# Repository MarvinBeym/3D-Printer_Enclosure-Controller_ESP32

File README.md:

# 3D Printer Enclosure Controller ESP32

***
This is an enclosure controller for 3d printers that runs on the dual core ESP32.

- It uses a Nextion NX4832T035 3.5inch 480px320p color touch TFT display.
- It also includes a simple Webinterface made with ESPUI for quick access without having to go to the display.

- ***For detailed information and images please see the [Wiki](https://github.com/MarvinBeym/3D-Printer_Enclosure-Controller_ESP32/wiki "Wiki").***
- ***STL files for 3D-Printing can be found on [Thingiverse](https://www.thingiverse.com/thing:4582196 "Thingiverse")***
***
You can currently choose between 2 versions.
1. The older cnc version
This is a bit older (the first one I made). Features haven't changed yet.
This is the version you want If you want to mill the pcb with a cnc mill because it is single side and has wider traces to make it easier for your mill.
2. The newest, pretiest pcb version
This is supposed to be made by a pcb factory like jlcpcb
It has text on it for all the components.
It also looks way better (I recommend ordering in black :D)

If you choose 2. -> I ordered mine from JLCPCB. The Gerber files are inside the Eagle folder (Gerber(vx.x.x).7z)
These were exported with the premade jlcpcb double sided cam processor. So you can just upload them to jlcpcb and order them.

***This project consists of 4 parts.***
1. The ESP32 software.
2. The Nextion display software (text, icons, images, ...).
3. The PCB.
4. The 3D Printed case to house everything.

***Features of this controller are:***
- 2x temperature and humidity sensors (DHT22).
- 2x 4-pin pwm fans.
- 1x Buzzer for alarms, warnings and such (currently not implemented as of v1.3.1).
- 1x 12v led strip connection controlled by a relay. This is usefull if you want to have a single color (like white).
- 1x 5V WS2812B single addressable led strip

***Software features:***
- ESPUI webinterface
- WifiManager creates a hotspot you can connect to that will make it possible to set the wifi network to connect to on boot.
- All values that can be changed can also be stored to flash. These values will be retrieved at boot and only saved using button pressed to prevent flash wear.
- Displaying of fan speed and percent.
- The possibility to change the speed of fans from 0% - 100%
- Displaying of sensor humidity and temperature
- Switching of 12v led strip.
- Graph for temperatures (only nextion display currently)
- Multiple modes choosable for WS2812B
  - (rainbow, fate, pulse, temperature (led strip is split in half showing temperature in color), running)
- Multiple colors choosable for WS2812B
- LCD Brighness
- LCD Sleep
- Temperature Warning and Danger 
  - (Currently do the same)
  - At some point Danger warning is supposed to do everything to make your notice something going wrong.
  - Like buzzer alarm, led blinking, display blinking and such. This is supposed to be used when something is seriously wrong > xyzTemperature.

***Notices:***
- The board uses a XL4015 buck converter which is rated for ~5A of power. 
- Make sure to choose an led strip that won't overload the converter. As this could lead to overheating.
- Also make sure to leave a bit of room for all other components like fans, 12v led strip, sensors and display.

- It is expecially important to make sure the Nextion display gets enough power.
- If your display starts showing weird graphics. DISCONNECT power immediately.
- Don't run the pcb from 5V pc usb port.
- Low current can destroy the display (although it never happened to me).

- Fan rpm could be off a bit as tacho reading is influenced by noise.
- The tacho ports both have an rc filter and most fans will work without a problem and will display the correct value.
- I have one fan (NF-F12 industrialPPC-3000) that will always display > 4500rpm. 
  - (should only have 3000rpm). 
  - I'm not sure if that is something caused by the fan itself.

***Credits:***
- Icons shown on the Nextion display are from https://icons8.com/

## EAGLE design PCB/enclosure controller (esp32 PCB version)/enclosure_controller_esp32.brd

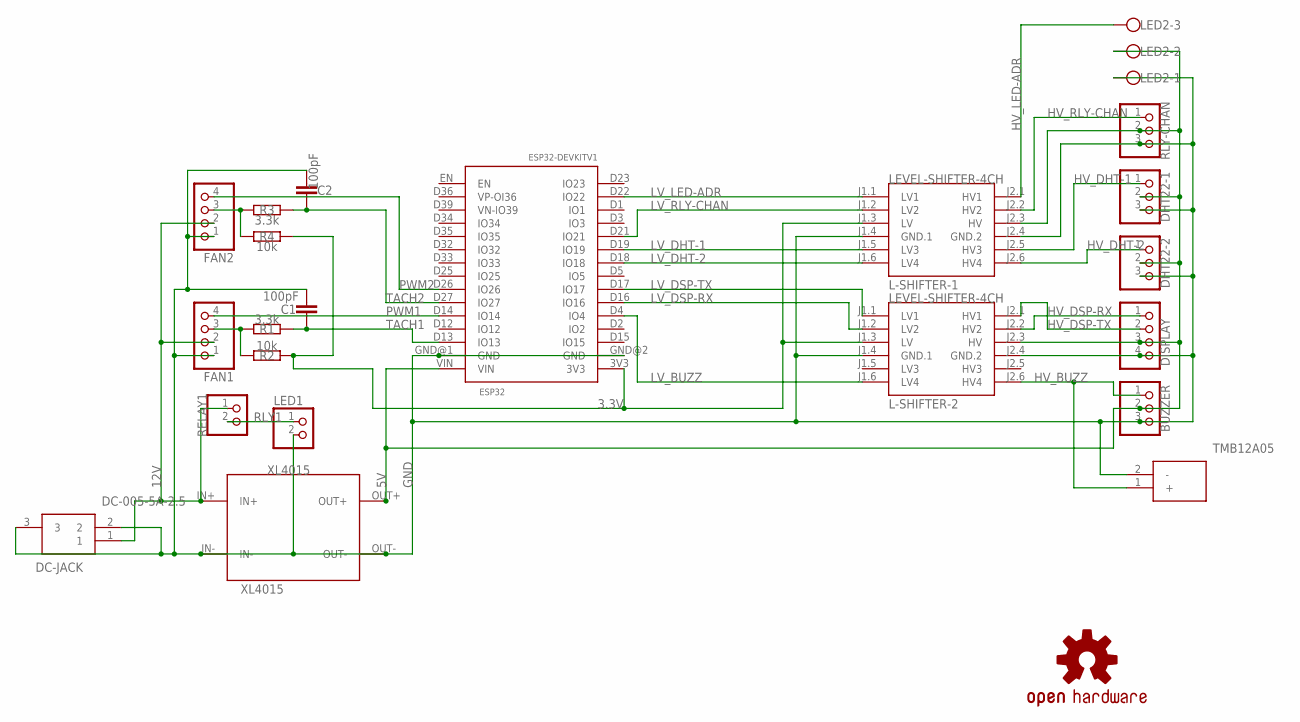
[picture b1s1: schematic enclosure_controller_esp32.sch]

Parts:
BUZZER: PINHD-1X3/OCT; 1X03/OCT
C1, C2: 100pF; C050-025X075
DC-JACK: DC-005-5A-2.5; DC0055A25
DHT22-1, DHT22-2: PINHD-1X3/OCT; 1X03/OCT
DISPLAY: PINHD-1X4/OCT; 1X04/OCT
ESP32: ESP32DEVKITV1; ESP32-DEVKITV1
FAN1, FAN2: PINHD-1X4/OCT; 1X04/OCT
L-SHIFTER-1, L-SHIFTER-2: LEVEL-SHIFTER-4CH
LED1: PINHD-1X2/OCT; 1X02/OCT
LED2: LED2-ADR; W237-103
LOGO1: OSHW-LOGOM; OSHW-LOGO-M
LS1: TMB12A05
R1, R3: 3.3k; 0207/10
R2, R4: 10k; 0207/10
RELAY1: PINHD-1X2/OCT; 1X02/OCT
RLY-CHAN: PINHD-1X3/OCT; 1X03/OCT
XL4015: XL4015

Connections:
3.3V: ESP32.3V3, L-SHIFTER-1.J1.3 (LV), L-SHIFTER-2.J1.3 (LV), R2.1, R4.1
5V: BUZZER.2, DHT22-1.2, DHT22-2.2, DISPLAY.3, ESP32.VIN, L-SHIFTER-1.J2.3 (HV), L-SHIFTER-2.J2.3 (HV), LED2.2, RLY-CHAN.2, XL4015.OUT+
12V: DC-JACK.1, FAN1.2, FAN2.2, RELAY1.1, XL4015.IN+
GND: BUZZER.3, C1.2, C2.1, DC-JACK.2, DC-JACK.3, DHT22-1.3, DHT22-2.3, DISPLAY.4, ESP32.GND@1 (GND), ESP32.GND@2 (GND), FAN1.1, FAN2.1, L-SHIFTER-1.J1.4 (GND.1), L-SHIFTER-1.J2.4 (GND.2), L-SHIFTER-2.J1.4 (GND.1), L-SHIFTER-2.J2.4 (GND.2), LED1.2, LED2.1, LS1.2 (-), RLY-CHAN.3, XL4015.IN-, XL4015.OUT-
HV_BUZZ: BUZZER.1, L-SHIFTER-2.J2.6 (HV4), LS1.1 (+)
HV_DHT-1: DHT22-1.1, L-SHIFTER-1.J2.5 (HV3)
HV_DHT-2: DHT22-2.1, L-SHIFTER-1.J2.6 (HV4)
HV_DSP-RX: DISPLAY.1, L-SHIFTER-2.J2.2 (HV2)
HV_DSP-TX: DISPLAY.2, L-SHIFTER-2.J2.1 (HV1)
HV_LED-ADR: L-SHIFTER-1.J2.1 (HV1), LED2.3
HV_RLY-CHAN: L-SHIFTER-1.J2.2 (HV2), RLY-CHAN.1
LV_BUZZ: ESP32.D4 (IO4), L-SHIFTER-2.J1.6 (LV4)
LV_DHT-1: ESP32.D19 (IO19), L-SHIFTER-1.J1.5 (LV3)
LV_DHT-2: ESP32.D18 (IO18), L-SHIFTER-1.J1.6 (LV4)
LV_DSP-RX: ESP32.D16 (IO16), L-SHIFTER-2.J1.2 (LV2)
LV_DSP-TX: ESP32.D17 (IO17), L-SHIFTER-2.J1.1 (LV1)
LV_LED-ADR: ESP32.D22 (IO22), L-SHIFTER-1.J1.1 (LV1)
LV_RLY-CHAN: ESP32.D21 (IO21), L-SHIFTER-1.J1.2 (LV2)
PWM1: ESP32.D14 (IO14), FAN1.4
PWM2: ESP32.D26 (IO26), FAN2.4
RLY1: LED1.1, RELAY1.2
TACH1: C1.1, ESP32.D13 (IO13), FAN1.3, R1.1, R1.2, R2.2
TACH2: C2.2, ESP32.D27 (IO27), FAN2.3, R3.1, R3.2, R4.2

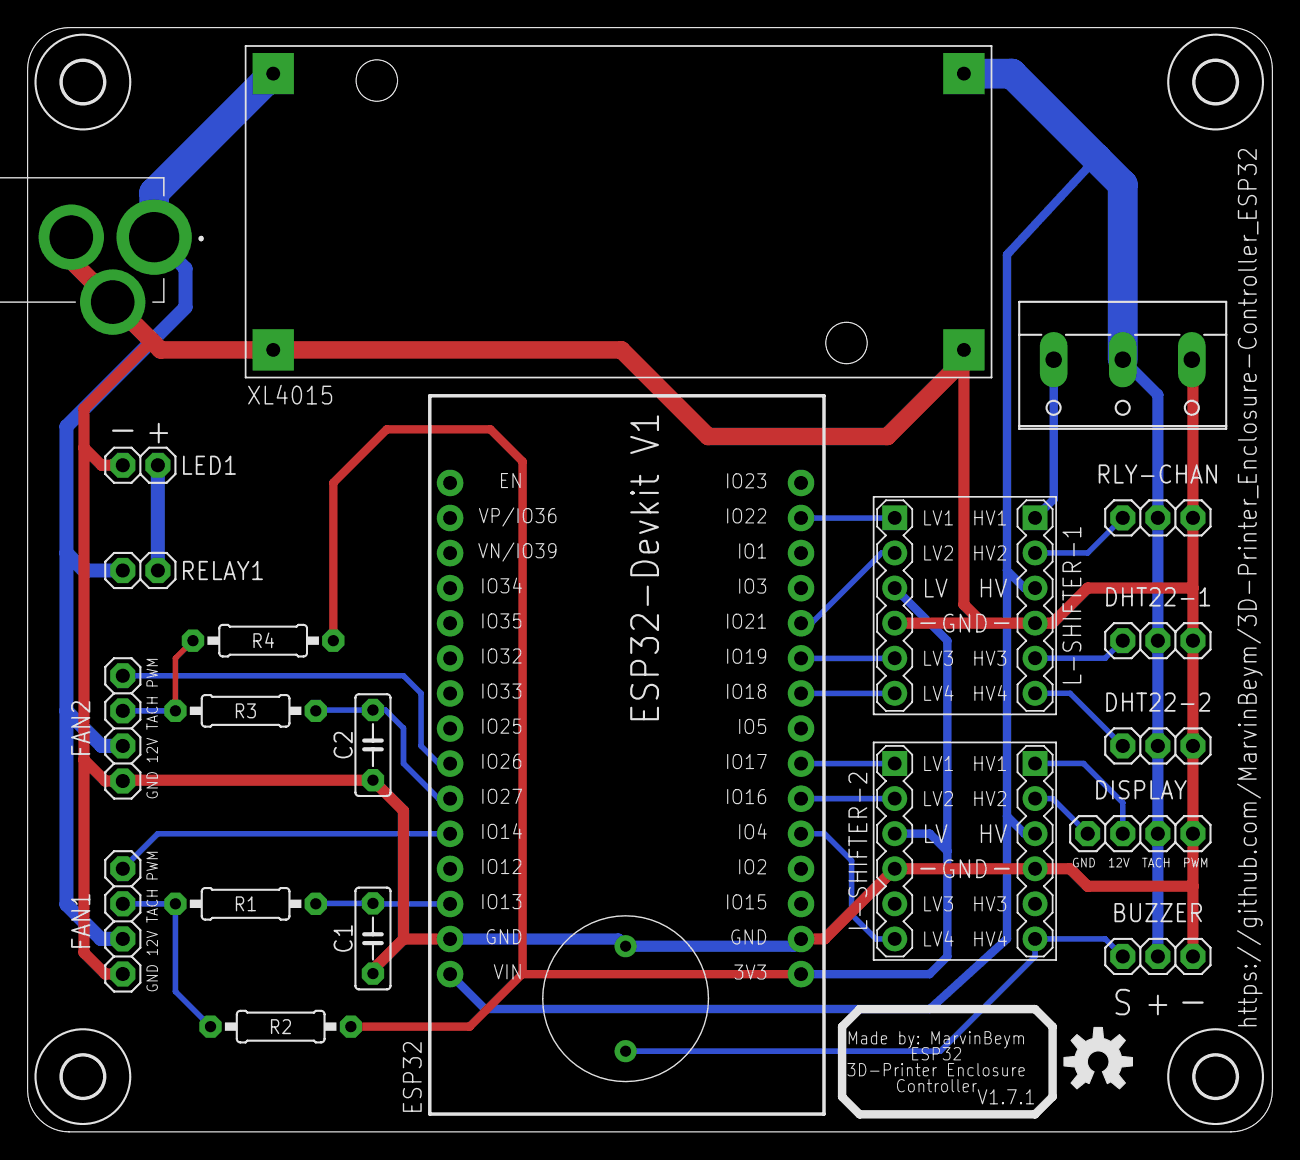
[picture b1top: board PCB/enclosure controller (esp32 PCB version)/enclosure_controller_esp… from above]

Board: 2 copper layers, 90.1 x 79.9 mm, 27 parts (0 on the bottom side), 23 nets.

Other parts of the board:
U$1, U$2, U$3, U$4: 3,0

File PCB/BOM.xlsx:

This file includes all components needed to assemble the pcb
Based on pcb version: 1.7.1
PCB itself
Position | Amount | Name | Value | Where to get (mostly banggood -> depending on your location you should look at 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
R1, R3 |  | Resistor 0207/10 or probably any other | 3.3k Ohm | https://www.banggood.com/Wholesale-Geekcreit-600pcs-30-Kinds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
R2, R4 |  | Resistor 0207/10 or probably any other | 10k Ohm
C1, C2 |  | Condensator C050-025X075 or probably any other | 100pF | https://www.banggood.com/1000Pcs-50-Value-50V-Ceramic-Capaci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
XL4015 | 1 | XL4015 buck converter (not the single chip) |  | https://www.banggood.com/XL4015-5A-DC-DC-Step-Down-Adjustabl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
DC-005-5A-2.5 | 1 | DC-005-5A-2.5 dc jack | 5A | https://lcsc.com/product-detail/AC-DC-Power-Plugs-Receptacle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
LED2-ADR | 1 | 3-Pin W237-103 = Screw terminal |  | https://www.banggood.com/10pcs-5mm-KF-301-3-Pin-PCB-Mount-Bl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
IN+, IN-, OUT+, OUT- | 4 | 1-Pin Male Header |  | https://www.banggood.com/10Pcs-40-Pin-2_54mm-Male-Female-SIL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
LED1, RELAY1 | 2 | 2-Pin Male Header
RLY-CHAN, DHT22-1, DHT22-2, BUZZER | 4 | 3-Pin Male Header
DISPLAY, FAN1, FAN2 | 3 | 4-Pin Male Header
L-SHIFTER-1, L-SHIFTER-2 | 4 | 6-Pin Female Header
ESP32 | 2 | 15-Pin Female Header
Other components (You can choose less/none for some)
 | 2 | DHT22 Temperature and Humidity Sensor (with Pullup on sensor) (you can solder y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 | NEEDS PULLUP | https://www.banggood.com/3Pcs-AM2302-DHT22-Temperature-And-H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
 | 1 | KY-019 (or any other) Relay (for 12V led |  | https://www.banggood.com/3Pcs-5V-Relay-5-12V-TTL-Signal-1-Ch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
 | 2 | 4-Pin PWM fans |  | Choose your own
 | 1 | ESP32 (30pin) |  | https://www.banggood.com/Geekcreit-ESP32-WiFi+bluetooth-Deve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
 | 1 | Buzzer (no use currently) either connected to BUZZER or below esp32 |  | Choose your own
 | 1 | 12 Power supply >5A | Recommend > 5A | Choose your own
 | 1 | WS2812B | DONT BUY RGBW | Choose your own based on liking
 | 1 | 12v Led strip |  | Choose your own based on liking

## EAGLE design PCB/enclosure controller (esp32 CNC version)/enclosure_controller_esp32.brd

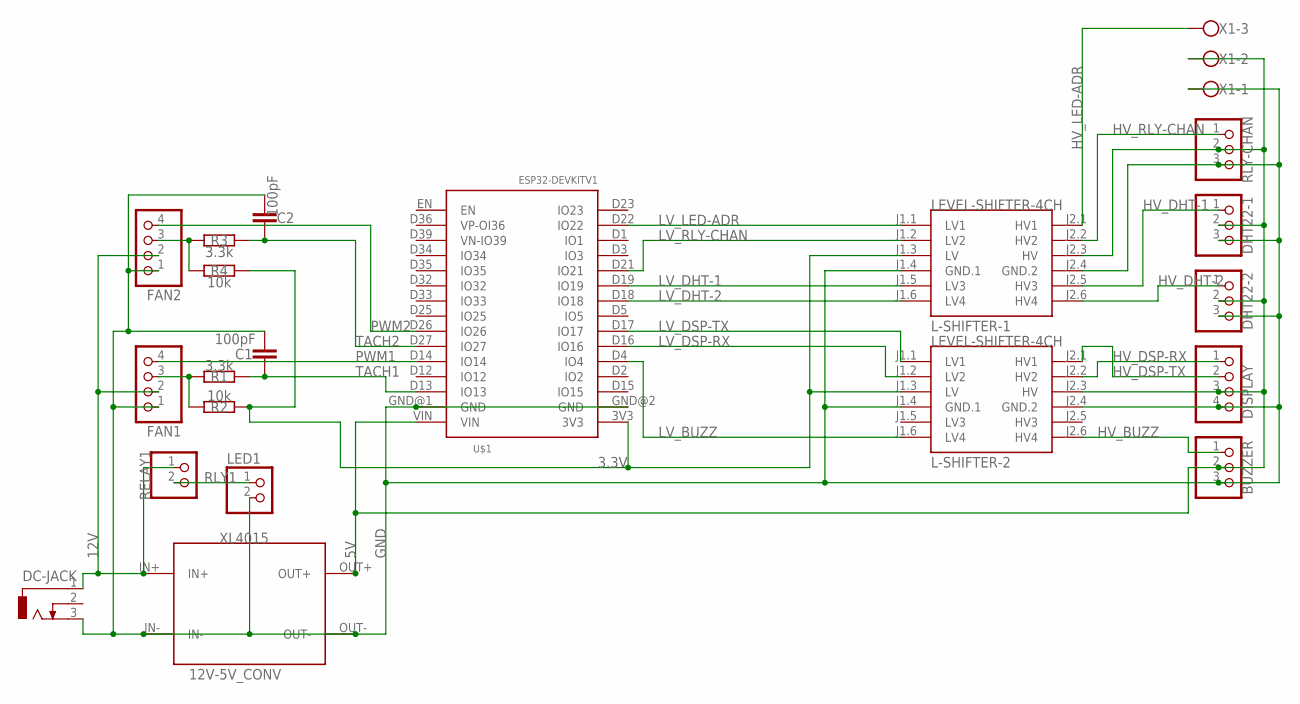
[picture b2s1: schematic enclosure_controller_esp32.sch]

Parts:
12V-5V_CONV: XL4015
BUZZER: PINHD-1X3; 1X03
C1, C2: 100pF; C050-025X075
DC-JACK: DCJ0303
DHT22-1, DHT22-2: PINHD-1X3; 1X03
DISPLAY: PINHD-1X4; 1X04
FAN1, FAN2: PINHD-1X4; 1X04
L-SHIFTER-1, L-SHIFTER-2: LEVEL-SHIFTER-4CH
LED1: PINHD-1X2; 1X02
R1, R3: 3.3k; 0207/10
R2, R4: 10k; 0207/10
RELAY1: PINHD-1X2; 1X02
RLY-CHAN: PINHD-1X3; 1X03
U$1: ESP32DEVKITV1; ESP32-DEVKITV1
X1: LED2-ADR; W237-103

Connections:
3.3V: L-SHIFTER-1.J1.3 (LV), L-SHIFTER-2.J1.3 (LV), R2.1, R4.1, U$1.3V3
5V: 12V-5V_CONV.OUT+, BUZZER.2, DHT22-1.2, DHT22-2.2, DISPLAY.3, L-SHIFTER-1.J2.3 (HV), L-SHIFTER-2.J2.3 (HV), RLY-CHAN.2, U$1.VIN, X1.2
12V: 12V-5V_CONV.IN+, DC-JACK.1, FAN1.2, FAN2.2, RELAY1.1
GND: 12V-5V_CONV.IN-, 12V-5V_CONV.OUT-, BUZZER.3, C1.2, C2.1, DC-JACK.3, DHT22-1.3, DHT22-2.3, DISPLAY.4, FAN1.1, FAN2.1, L-SHIFTER-1.J1.4 (GND.1), L-SHIFTER-1.J2.4 (GND.2), L-SHIFTER-2.J1.4 (GND.1), L-SHIFTER-2.J2.4 (GND.2), LED1.2, RLY-CHAN.3, U$1.GND@1 (GND), U$1.GND@2 (GND), X1.1
HV_BUZZ: BUZZER.1, L-SHIFTER-2.J2.6 (HV4)
HV_DHT-1: DHT22-1.1, L-SHIFTER-1.J2.5 (HV3)
HV_DHT-2: DHT22-2.1, L-SHIFTER-1.J2.6 (HV4)
HV_DSP-RX: DISPLAY.1, L-SHIFTER-2.J2.2 (HV2)
HV_DSP-TX: DISPLAY.2, L-SHIFTER-2.J2.1 (HV1)
HV_LED-ADR: L-SHIFTER-1.J2.1 (HV1), X1.3
HV_RLY-CHAN: L-SHIFTER-1.J2.2 (HV2), RLY-CHAN.1
LV_BUZZ: L-SHIFTER-2.J1.6 (LV4), U$1.D4 (IO4)
LV_DHT-1: L-SHIFTER-1.J1.5 (LV3), U$1.D19 (IO19)
LV_DHT-2: L-SHIFTER-1.J1.6 (LV4), U$1.D18 (IO18)
LV_DSP-RX: L-SHIFTER-2.J1.2 (LV2), U$1.D16 (IO16)
LV_DSP-TX: L-SHIFTER-2.J1.1 (LV1), U$1.D17 (IO17)
LV_LED-ADR: L-SHIFTER-1.J1.1 (LV1), U$1.D22 (IO22)
LV_RLY-CHAN: L-SHIFTER-1.J1.2 (LV2), U$1.D21 (IO21)
PWM1: FAN1.4, U$1.D14 (IO14)
PWM2: FAN2.4, U$1.D26 (IO26)
RLY1: LED1.1, RELAY1.2
TACH1: C1.1, FAN1.3, R1.1, R1.2, R2.2, U$1.D13 (IO13)
TACH2: C2.2, FAN2.3, R3.1, R3.2, R4.2, U$1.D27 (IO27)

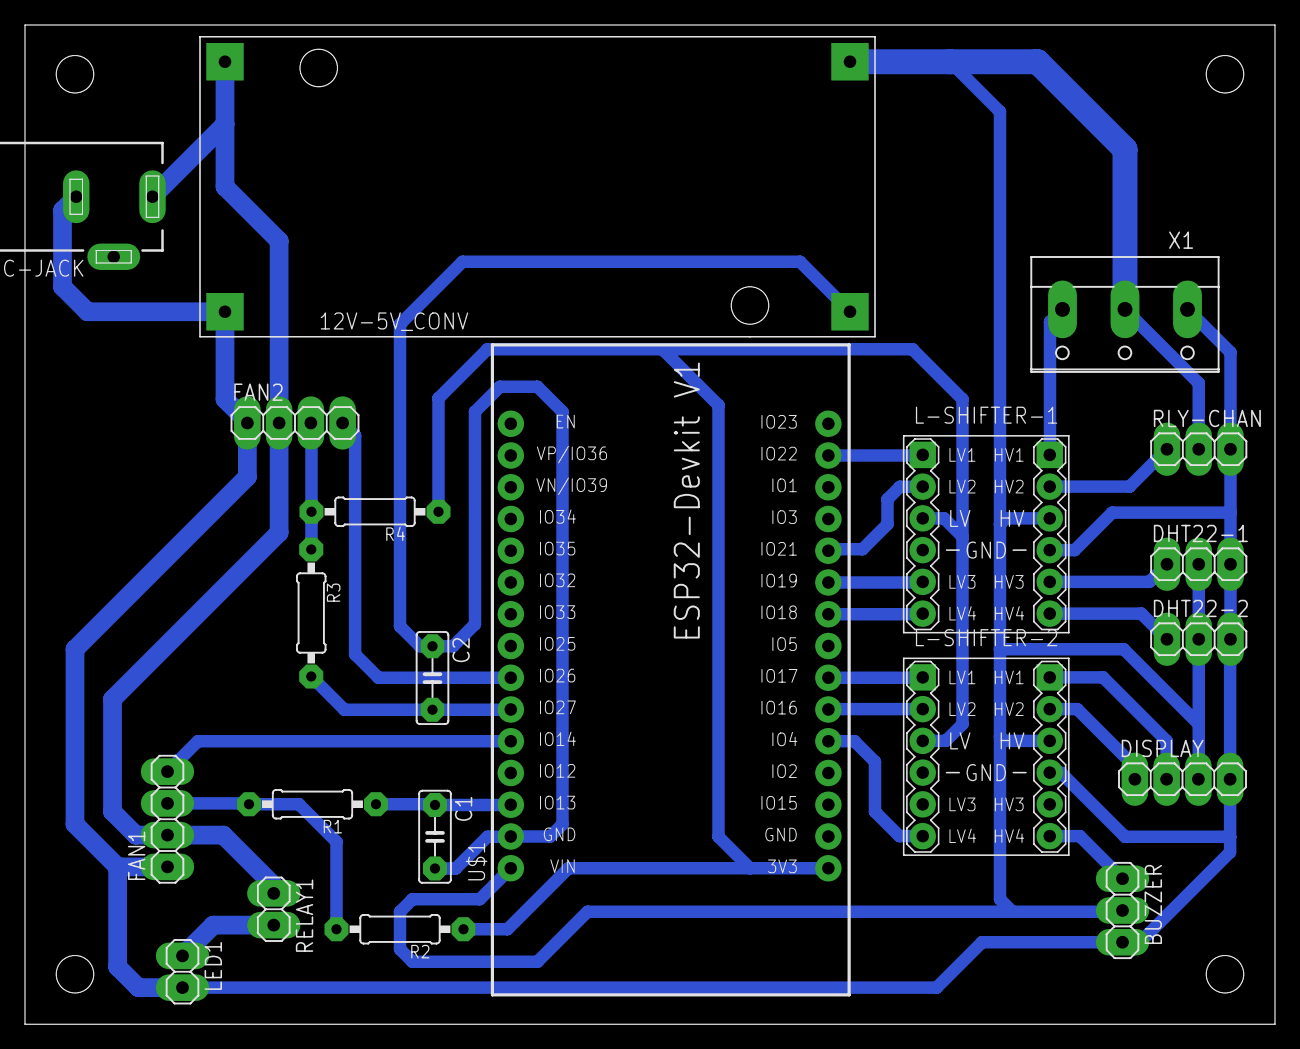
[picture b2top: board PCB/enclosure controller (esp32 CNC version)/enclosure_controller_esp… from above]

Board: 2 copper layers, 100.0 x 79.9 mm, 21 parts (0 on the bottom side), 23 nets.

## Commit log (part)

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2020-07-21 gitignore commit
2020-07-21 added about page. Changed version to 1.1
2020-07-22 updated display software. Fixed led2 mode problems some code improvements (switch). added more animations. added first parts for temperature warning.
2020-07-23 Added Temperature Warning. Added buzzer logic for Temperature Danger. Cleaned up code a bit.
2020-07-23 Fixed fan2 pwm setting. fan2 was setting the dutyCycle of fan1.
2020-07-28 fixed display sleep not working when using espui
2020-07-28 Fixed espui button/switch again. Renamed switches from espui to espui_switch_... Added about tab content Added reboot button to espui Added configurable reboot to rather reboot than create hotspot.
2020-07-28 Added WiFiManager Removed old Wifi logic. Removed fixed wifi ssid and password. Added description to configuration options. Added wifi reset button to espui
2020-07-28 Added WifiManager dark mode
2020-07-29 Added temperature animation for led2. Renamed configuration for min temp
2020-07-29 Fixed led2 mode changing not reseting color
2020-07-29 Added "needs led2 color to modes that need a color Moved rainbow mode to the bottom
2020-07-29 Fixed led2 mode not loading
2020-08-26 Project cleanup.
2020-08-26 Fixed .gitignore setup beeing wrong
2020-08-26 .gitignore fix
2020-08-26 Removed fans max rpm configuration.
2020-08-27 Moved some defines to new file ESP32 changes: Removed changing of button state on display Fixed led2 setting color not working like it should for black (off). Fixed led2 brightness not beeing 100% wh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
2020-08-27 Fixed wrong brighness method on color setting.
2020-08-27 Updated Nextion Software file to 1.3.1
2020-08-27 Added GPLv3 Licence notice to the top of all files
2020-08-27 Update README.md
    fixed formatting of readme
2020-08-28 added PCB files. 1. The quality pcb files for ordering 2. The cnc pcb files for milling using a cnc mill (wider traces) this file is a bit older but is still working.
2020-08-28 Added fusion360 3d files both for pcb and cnc version
2020-08-28 Updated .gitignore to include BOM edit file Added BOM file for needed components (pcb version)
2020-08-28 removed message page image
2020-08-28 Added image of pcb without components
2020-08-29 Fixed issue with degrees symbol on nextion display. Fixed sensor 2 setting values for sensor 1 on display. Changed check if dht value read is nan to atleast set the value that already works. Added Te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
2020-08-29 Changed Nextion tft file to include current version.
2020-08-29 Fixex WifiManager development version lib_deps Added FastLED to lib_deps Removed upload_port from platform.ini
2020-08-30 Big changes incomming. Replaced original effects logic with dynamic loading of effects. Effects can now be self added and will be made available both tho the display and the ESPUI. Replaced storing/c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
2020-08-30 Fix for new led effects logic. Added check if mode selected is larger than maximum (-1) Added check if current mode is not equal to "new" mode and only update animation then.
2020-08-30 Removed unneded include Arduino.h from effect class files. Added example pictures for creating effects
2021-04-02 Started reworking the firmware.
    - Moved some features to there own class.
    - Removed all the code and started from the beginning to reduce early created errors.
    - Implemented first basic features (sensor, fan, led1 relay, led2)
2021-04-03 Improved Sensor class.
    - Now .handle() call required.
    - Now uses esp32's tasks to read the sensor every <sense interval>.
    Fixed sense interval in config set to long instead of int.
2021-04-03 Added small delay after creating fan. Worked on implementing Nextion Display.
    - Added small delay after fan object creation just to make sure it won't cause trouble.
    - Implemented first functions for NextionDisplay.
2021-04-03 Updated gitignore to include .idea folder.
2021-04-03 Reformatted code and fixed some spelling errors.
2021-04-04 Added begin functions to classes to fix errors. Added nextion handling.
    - Fixed sensors always reading NaN (0.00 °C).
    - Added command handling for nextion display
    - Reworked how messages are send from the nextion display (made all components vscope global)
    - Removed all the code from the nextion display.
    - Nextion is now fully handled by ESP32 to prevent issues with communication.
2021-04-04 Added logic for handling sliders for fan speed. Changed parameter compName to compVarName.
2021-04-04 Added esp8266-react as a webinterface.
    - Added esp8266-react and created/designed first pages.
    - Removed no longer used libs from platformio.ini (ESPUI, WifiManager, ...)
    - Moved general environment configuration in platformio.ini to the [env] environment
2021-04-05 Added sensor temperature graphs to sensor tab.
2021-04-05 Designed the sensors page and added react redux + redux-toolkit to save data between pages.
2021-04-06 Improved styling of fans page. Added ability to add className to value field component.
2021-04-06 Improved value field with optional end adornment image or text.
2021-04-06 Improved ValueField component and added value fields to sensors page.
2021-04-06 Removed some unused variables.
2021-04-06 Created main tab design.
2021-04-06 Added code for changing the fan speed from the webinterface.
2021-04-06 Moved classes to libs folder.
2021-04-06 Added ability to configure what features to enable.
2021-04-06 Fixed nextion display no longer working (whoops).
2021-04-06 Fixed setSpeed rest request not working
2021-04-07 Correctly disabled features of webinterface.
2021-04-07 Removed end adornment from duty cycle value field. Fixed QuickLineChart component throwing errors.
2021-04-07 Implemented EffectLoader for led2 effects.
2021-04-07 Improved led1 & led2 responses and webinterface usage.
2021-04-08 Added ability to check if sensor temperature or humidity changed. Improved nextion temp & humidity update.
2021-04-08 Changed sensors to use callback tasks when value changed.
2021-04-08 Finally found reason why esp32 kept loosing heap. Changed fan task to include a vTaskDelay to give the idle task some cpu time.
2021-04-09 Removed configuration temporarily to make debugging easier.
2021-04-09 Optimized fan class a bit more.
2021-04-09 Removed unneeded xyzClass::taskfunction from xTaskCreate.
2021-04-10 Added event usage to sensor class.
    - Sensor class now also uses events that get set when the temperature should update.
2021-04-10 Improved relay class code.
2021-04-10 Changed nextion display to also use task events
2021-04-11 Added pwm update callback and event to fan. Fixed task event bits being wrong.
    - Added pwm callback that waits for the event to get triggered by the fans setDutyCycle or setPercent function.
    - Fixed setDutyCycle function not updating percent value
    - Fixed task event bits being wrong (they had to be unique) :D
2021-04-11 Added flags to event loaders addToJson function. Enabled Wifi and Webinterface again.
2021-04-12 Websocket implementation for fans. - Added react env variable for redux-websocket prefix. - Added sync of percent, rpm and duty cycle to fans page. - Added back web socket message handling.
2021-04-14 Changed char* to const char* for components. Removed or commented out some lines to remove warning for unused variables/code,
2021-04-17 Fix for redux-toolkit default middleware and dispatch improvement.
    - Implemented dispatch prevention. A dispatch can now only be executed when the command hasn't been recently executed (gets reset by middleware).
    - Fixed issue with redux-toolkit createAsyncThunk not working.
2021-04-17 Renamed, moved and removed some of the the icons used on the display.
2021-04-17 Fixed wrong icon color. Increased size of arrows for the led2 mode switching.
2021-04-17 Created newMap function that replaces the arduino map and makes sure the values don't exceed outMin and outMax.
2021-04-17 Converted helper file to a class to allow multi inclusion.
2021-04-17 Main page with websocket and improvements
    - Changed main page to use websocket instead of no longer used/working rest api call.
    - Added redux select to get both sensors as an array (selectSensors).
    - Improved ValueField component to use up 100% width when nothing else is there.
    - Updated nextion file with latest changes.
2021-04-17 Added missing #pragma once
2021-04-17 Worked on implementing a way to create forms from the configSetup for the solid effect.
2021-04-18 Effect update handling and fixing
    - Fixed wrong message when invalid component or invalid command send (would send int instead of name of component as string).
    - Added wsSend for effect config changing.
2021-04-18 Changed development env ip
2021-04-18 Added updating of the Led2EffectConfigForm when the state changes.
    - Will update the form for all currently connected websockets (so that users don't have to refresh the page to see the changes live).
2021-04-19 Changed switch field to also use "value" for storing the current value instead of "state".
2021-04-19 Added white color to solid effect, changed pink color, changed orange color.
2021-04-19 Moved config field functions to protected.
2021-04-19 Changed some variable names and function parameter names.
2021-04-19 Set default min and max value. Min & Max will only show when different from the normal integer min & max.
2021-04-19 Added effect config to rainbow effect.
2021-04-19 Fixed switching from a different effect to the "none" effect causing react exception.
2021-04-19 Changed effect to no longer require an overridden function that tells if the effect has a config.
2021-04-20 Created card component and replaced PaperSection on sensor page with cards
2021-04-20 Moved graphs to new component LineChartCard that displays the chart in a card.
2021-04-21 Replaced PaperSection with new Card component. Added TabContent component as the base component for all tabs.
2021-04-21 Replaced PaperSection with new Card component on Main tab.
2021-04-21 Updated leds page with new Card component.
2021-04-21 Fixed formatting in Main component.
2021-04-21 Removed no longer used PaperSection component.
2021-04-21 Added animation to led 2 effect configuration. Added missing default state for selects array.
2021-04-24 Increased slider card padding left & right.
2021-04-24 Added grid template to configuration tab.
2021-04-24 Add switch for disabling fan spin animation
2021-04-24 Add SelectCard component and defaultPage configuration.
2021-04-24 Add disabling fan spin animation
2021-04-24 Convert EnclosureController component into component using hooks.
2021-04-24 Change file extension of EnclosureController component to js (javascript)
2021-04-24 Add default page redirect from webinterface config state.
2021-04-24 Added show sensor graph config fields.
2021-04-24 Added rendering sensor graphs if enabled in webinterface config.
2021-04-24 Remove unused regex webserver request build_flag
2021-04-26 Create Buzzer class.
2021-04-26 Added warning fields to sensor slice
2021-04-26 Renamed temp warn in sensor state to "tempWarn" instead of "warning"
2021-04-26 Added InputCard component.
2021-04-26 Replaced mapping for sensor fields to manual creation of all fields.
2021-04-26 Added temp warning handling to esp32 code.
2021-04-26 Added sending of temp warning over websocket. Fixed wrong object name for tempWarn.
2021-04-26 Changed SwitchCard component to return value in onChange instead of event.
2021-04-26 Changed leds page to use SelectCard component for led2 effect.
2021-04-26 Added borders around sensor card when warning got triggered. Fixed sensor2 updates sending wrong data.
2021-04-26 Added updating of the exceeded state when tempWarn ist modified.
2021-04-26 Buzzer changes.
2021-04-26 Replaced temp warning & temp danger with single temp danger.
2021-04-26 Changed ValueField component to ValueCard component.
2021-04-26 Moved temperature danger into sub card.
2021-04-26 Changed order

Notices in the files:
README.md:
License: GPL v3
parts and their libraries:
diy-modules: Released under the Creative Commons Attribution 4.0 International License: http://creativecommons.org/licenses/by/4.0
SparkFun-Aesthetics: Licensing: Creative Commons ShareAlike 4.0 International - https://creativecommons.org/licenses/by-sa/4.0
